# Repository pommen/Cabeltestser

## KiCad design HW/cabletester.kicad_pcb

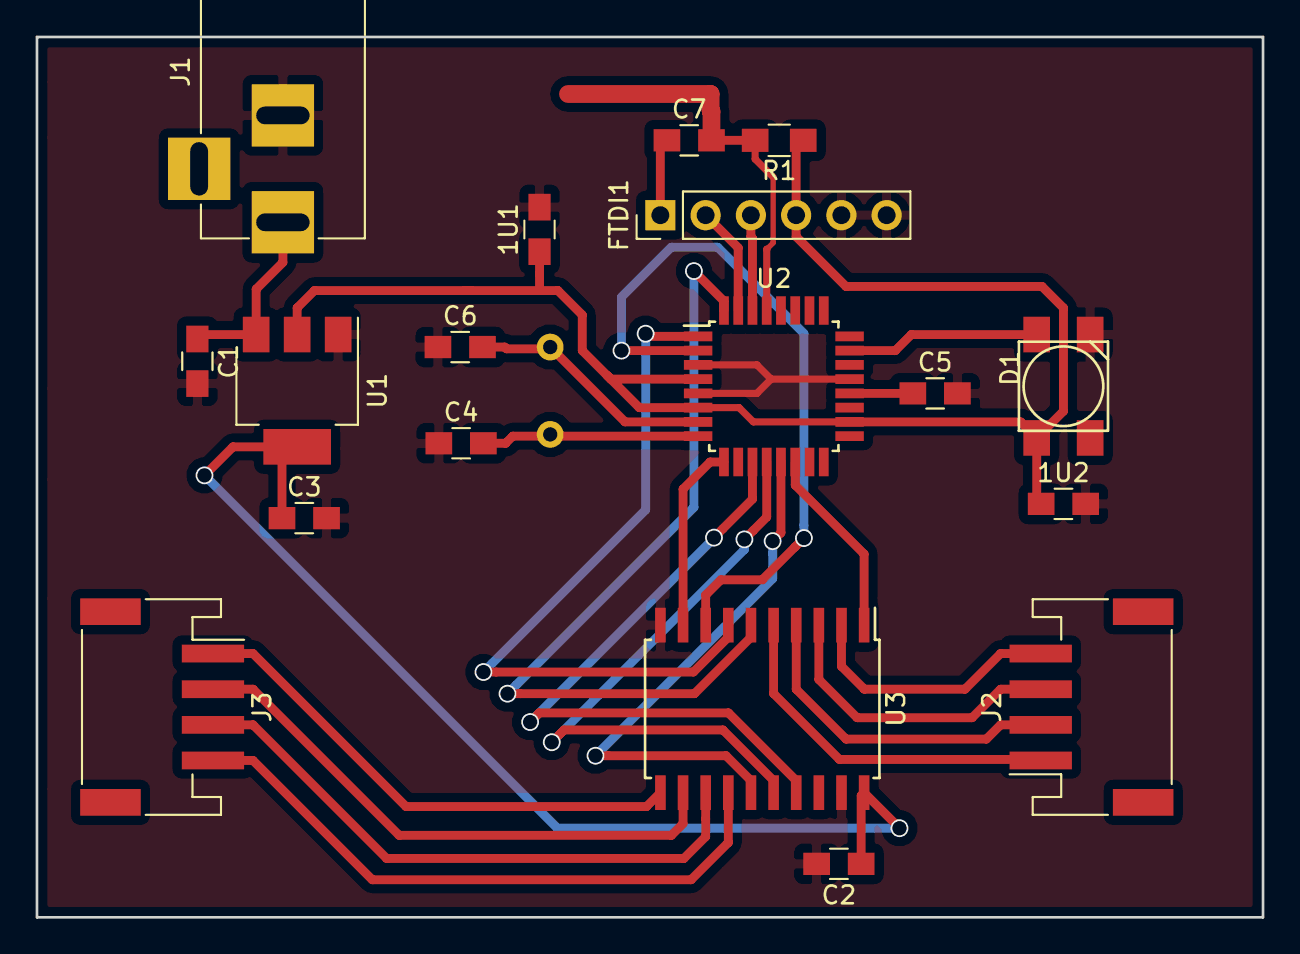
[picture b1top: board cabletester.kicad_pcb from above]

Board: 2 copper layers, 68.8 x 49.4 mm, 19 parts (1 on the bottom side), 28 nets.

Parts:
1U1, 1U2: 0,1U; C_0805_HandSoldering
C1, C2, C3: C; C_0805_HandSoldering
C4, C6: 22pf; C_0805_HandSoldering
C5: 0,1U; C_0805_HandSoldering
C7: 0,1u; C_0805_HandSoldering
D1: WS2812B
FTDI1: FTDI; Pin_Header_Straight_1x06_Pitch2.54mm
J1: Barrel_Jack; BARREL_JACK
J2, J3: Conn_01x04; JST_PH_S4B-PH-SM4-TB_04x2.00mm_Angled
R1: 10K; R_0805_HandSoldering
U1: AMS117-5.0; SOT-223
U2: ATMEGA328P-AU-Arduino; TQFP-32_7x7mm_Pitch0.8mm
U3: 74HCT541; SOIC-20W_7.5x12.8mm_Pitch1.27mm
Y1: 8MHZ; Crystal_HC18-U_Vertical

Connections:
1: U2.32, U3.6
2: U2.1, U3.7
3: U2.2, U3.8
4: U2.9, U3.9
11: U2.10, U3.18
12: U2.11, U3.17
13: U2.12, U3.16
14: U2.13, U3.15
GND: 1U1.2, 1U2.2, C1.2, C2.2, C3.2, C4.1, C5.2, C6.1, D1.1, FTDI1.5, FTDI1.6, J1.2, U1.1, U2.3, U2.5, U2.21, U3.10, U3.19
unnamed: C1.1, J1.1, U1.3
unnamed: C4.2, U2.7, Y1.1
unnamed: C5.1, U2.20
unnamed: C6.2, U2.8, Y1.2
unnamed: J2.1, U3.5
unnamed: J2.2, U3.4
unnamed: J2.3, U3.3
unnamed: J2.4, U3.2
unnamed: J3.1, U3.11
unnamed: J3.2, U3.12
unnamed: J3.3, U3.13
unnamed: J3.4, U3.14
RST: C7.1, FTDI1.1
RXI: FTDI1.3, U2.30
TX0: FTDI1.2, U2.31
VCC: 1U1.1, 1U2.1, C2.1, C3.1, D1.3, FTDI1.4, R1.1, U1.2, U1.4, U2.4, U2.6, U2.18, U3.20
en: U2.14, U3.1
led: D1.2, U2.23
reset_in: C7.2, R1.2, U2.29
